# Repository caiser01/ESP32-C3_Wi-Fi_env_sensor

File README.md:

# ESP32-C3 Wi-Fi environment sensor node
<p>A Wi-Fi connected temperature, humidity, and pressure sensor node based around the Espressif ESP32-C3-MINI-1 and the Bosch BME280 Humidity/Pressure/Temperature sensor.</p>

<p>The primary goal of this project is to provide a simple platform for monitoring the temperature and humidity of the spaces inside one's home. These wireless sensor nodes can be easily integrated with the free software packages such as Home Assistant (https://www.home-assistant.io) and ESPHome (https://esphome.io). Alternatively, the user can write their own fully custom firmware using ESP-IDF, Arduino, or MicroPython.</p>

<p>Through simple monitoring of the temperature and humidity in the different rooms of one's home it is possible to:
<br>
<ul>
  <li>Gain insight into the effectiveness of the home's heating and cooling (HVAC) system</li>
  <li>Determine if a space may need a humidifier/dehumidifier</li>
  <li>Identify spaces that may need additional insulation</li>
  <li>Find spaces with doors or windows that do not seal tightly</li>
</ul>
</p>
<p>Additionally, the barometric pressure sensing capability can provide realtime insight into changing local weather conditions.</p>

## Design
<p>This device was designed for measuring the basic ambient environmental conditions of an indoor space so that they may be remotely displayed instantly and/or logged for long-term monitoring. The ESP32-C3-MINI-1 was chosen for its small footprint and the numerous available coding frameworks including ESP-IDF, Arduino, MicroPython, and ESPHome. The device includes a built in charger for a lithium battery. The user has the option to power the sensor node from a USB-C cable or from a rechargeable lithium battery. Firmware flashing is also performed through the USB-C connector via the ESP32-C3's built in USB interface. Depending on the software and framework used, over-the-air (OTA) firmware flashing is also possible via Wi-Fi.</p>

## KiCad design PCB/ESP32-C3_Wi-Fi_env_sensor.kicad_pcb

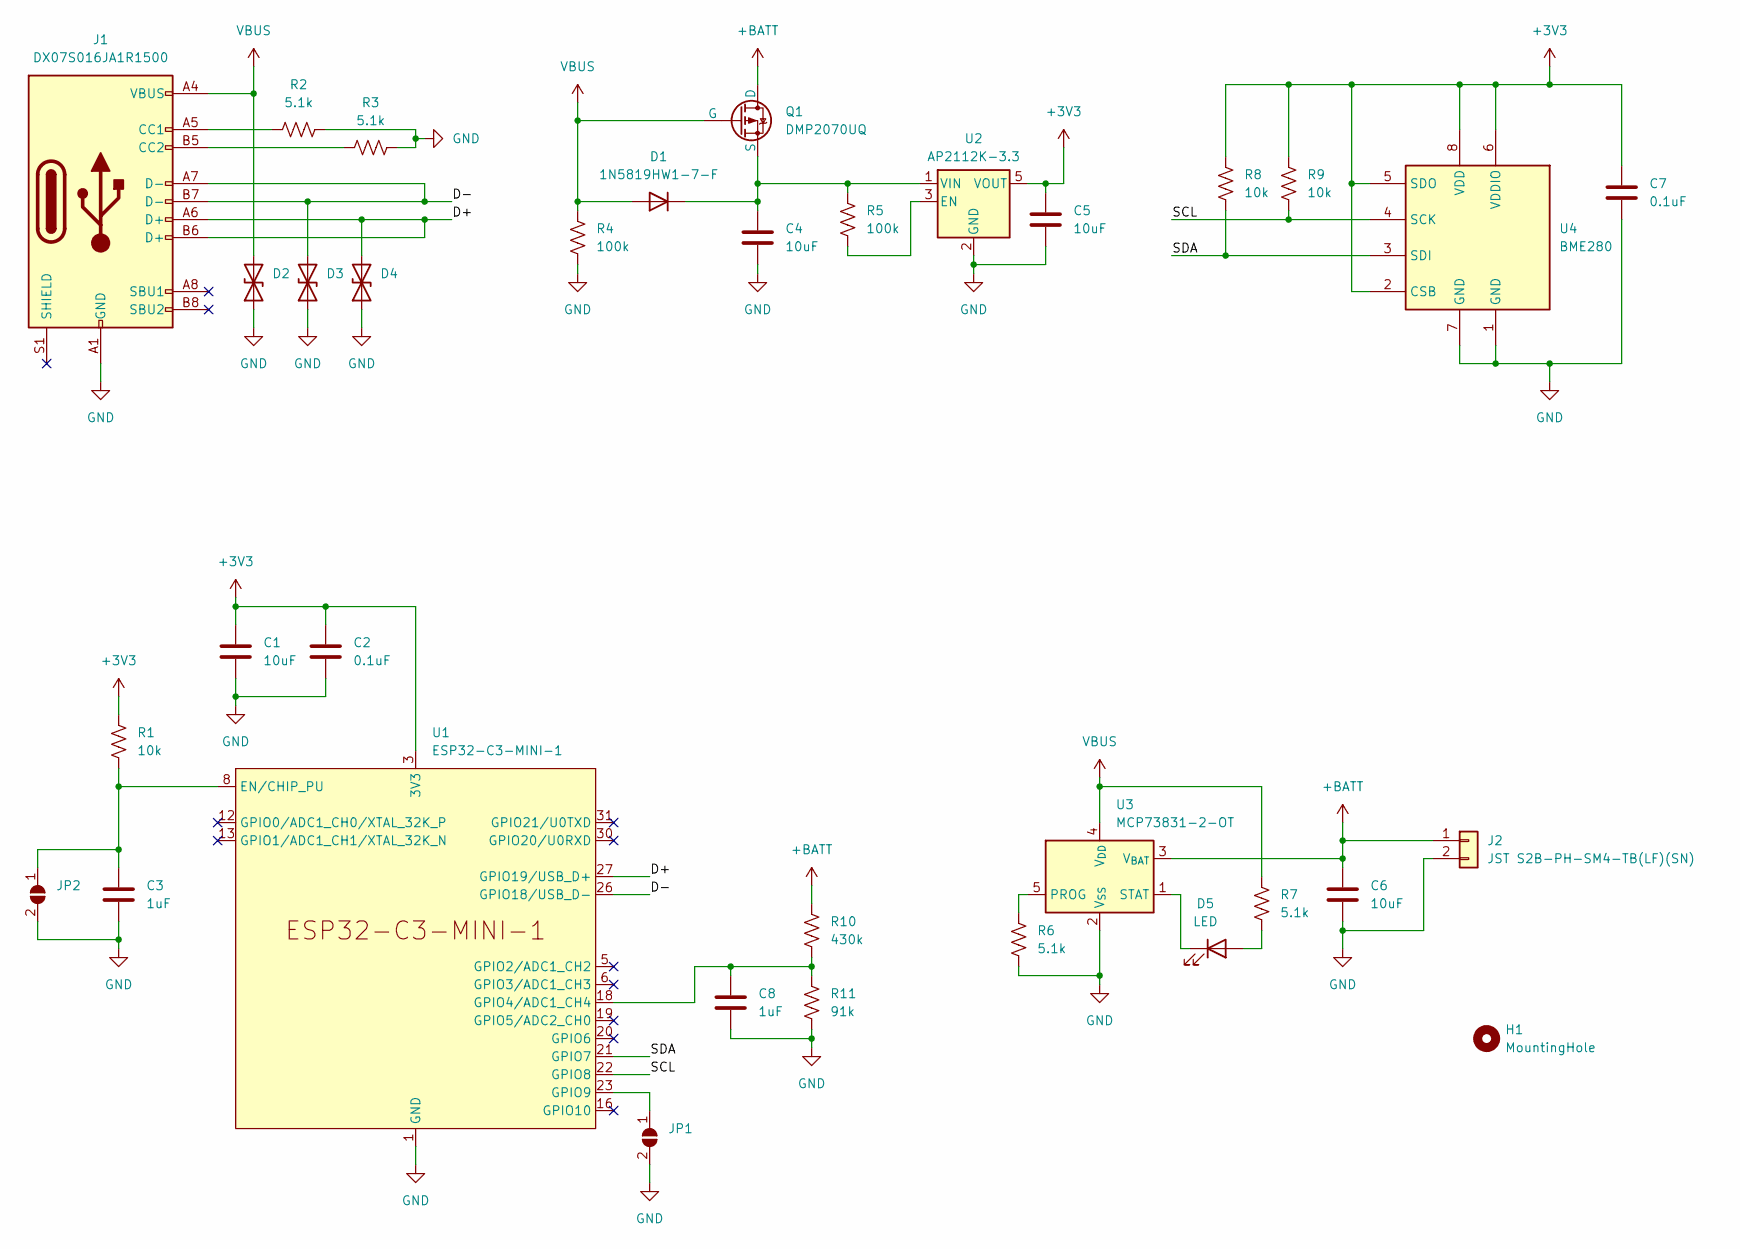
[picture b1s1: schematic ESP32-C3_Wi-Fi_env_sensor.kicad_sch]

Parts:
C1, C4, C5, C6: 10uF; C_0603_1608Metric_Pad1.08x0.95mm_HandSolder
C2, C7: 0.1uF; C_0603_1608Metric_Pad1.08x0.95mm_HandSolder
C3, C8: 1uF; C_0603_1608Metric_Pad1.08x0.95mm_HandSolder
D1: 1N5819HW1-7-F; D_SOD-123F
D2, D3, D4: LESD5D5.0CT1G; D_SOD-523
D5: LED; LED_0603_1608Metric_Pad1.05x0.95mm_HandSolder
H1: MountingHole; MountingHole_2.7mm_M2.5
J1: DX07S016JA1R1500; USB_C_Receptacle_JAE_DX07S016JA1R1500
J2: JST S2B-PH-SM4-TB(LF)(SN); JST_PH_S2B-PH-SM4-TB_1x02-1MP_P2.00mm_Horizontal
JP1, JP2: SolderJumper_2_Open; SolderJumper-2_P1.3mm_Open_Pad1.0x1.5mm
Q1: DMP2070UQ; SOT-23
R1, R8, R9: 10k; R_0402_1005Metric_Pad0.72x0.64mm_HandSolder
R2, R3, R6, R7: 5.1k; R_0603_1608Metric_Pad0.98x0.95mm_HandSolder
R4, R5: 100k; R_0603_1608Metric_Pad0.98x0.95mm_HandSolder
R10: 430k; R_0603_1608Metric_Pad0.98x0.95mm_HandSolder
R11: 91k; R_0603_1608Metric_Pad0.98x0.95mm_HandSolder
U1: ESP32-C3-MINI-1
U2: AP2112K-3.3; SOT-23-5
U3: MCP73831-2-OT; SOT-23-5
U4: BME280; Bosch_LGA-8_2.5x2.5mm_P0.65mm_ClockwisePinNumbering

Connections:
+3V3: C1.1, C2.1, C5.1, C7.1, R1.1, R8.1, R9.1, U1.3 (3V3), U2.5 (VOUT), U4.2 (CSB), U4.5 (SDO), U4.6 (VDDIO), U4.8 (VDD)
+BATT: C6.1, J2.1, Q1.3 (D), R10.1, U3.3 (V_{BAT})
/D+: D4.2 (A2), J1.A6 (D+), J1.B6 (D+), U1.27 (GPIO19/USB_D+)
/D-: D3.2 (A2), J1.A7 (D-), J1.B7 (D-), U1.26 (GPIO18/USB_D-)
/SCL: R9.2, U1.22 (GPIO8), U4.4 (SCK)
/SDA: R8.2, U1.21 (GPIO7), U4.3 (SDI)
GND: C1.2, C2.2, C3.2, C4.2, C5.2, C6.2, C7.2, C8.2, D2.1 (A1), D3.1 (A1), D4.1 (A1), J1.A1 (GND), J1.A12 (GND), J1.B1 (GND), J1.B12 (GND), J2.2, JP1.2 (B), JP2.2 (B), R2.2, R3.2, R4.2, R6.2, R11.2, U1.1 (GND), U1.2 (GND), U1.11 (GND), U1.14 (GND), U1.36 (GND), U1.37 (GND), U1.38 (GND), U1.39 (GND), U1.40 (GND), U1.41 (GND), U1.42 (GND), U1.43 (GND), U1.44 (GND), U1.45 (GND), U1.46 (GND), U1.47 (GND), U1.48 (GND), U1.49 (GND), U1.50 (GND), U1.51 (GND), U1.52 (GND), U1.53 (GND), U2.2 (GND), U3.2 (V_{SS}), U4.1 (GND), U4.7 (GND)
unnamed: C4.1, D1.1 (K), Q1.2 (S), R5.2, U2.1 (VIN)
unnamed: D5.2 (A), R7.2
unnamed: D5.1 (K), U3.1 (STAT)
unnamed: J1.A5 (CC1), R2.1
unnamed: J1.B5 (CC2), R3.1
unnamed: JP1.1 (A), U1.23 (GPIO9)
unnamed: C3.1, JP2.1 (A), R1.2, U1.8 (EN/CHIP_PU)
unnamed: C8.1, R10.2, R11.1, U1.18 (GPIO4/ADC1_CH4)
unnamed: R5.1, U2.3 (EN)
unnamed: R6.1, U3.5 (PROG)
VBUS: D1.2 (A), D2.2 (A2), J1.A4 (VBUS), J1.A9 (VBUS), J1.B4 (VBUS), J1.B9 (VBUS), Q1.1 (G), R4.1, R7.1, U3.4 (V_{DD})

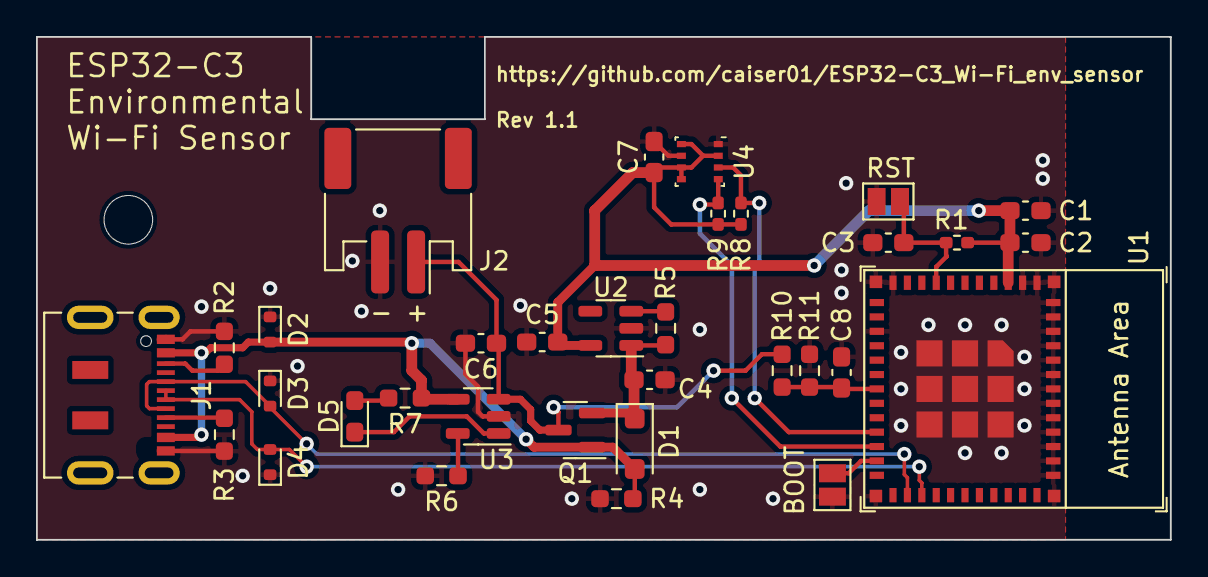
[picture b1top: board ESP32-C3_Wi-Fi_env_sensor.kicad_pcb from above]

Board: 2 copper layers, 63.0 x 27.9 mm, 34 parts (0 on the bottom side), 18 nets.

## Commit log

2024-09-19 Add .gitignore
2024-09-19 Add KiCad PCB files
2024-09-19 Setup CAM output per PCBWay's instructions
2024-10-15 Move U2, R5, C4 to make C4 more effective
2024-10-15 Add base example for ESPHome
2024-10-16 Add revision 1.0 board photo
2024-10-16 Add photo of revision 1.0 PCB to README.md
2024-10-16 Add Arduino test program
2024-10-16 Change framework from esp-idf to arduino
2024-10-16 Expand README.md
